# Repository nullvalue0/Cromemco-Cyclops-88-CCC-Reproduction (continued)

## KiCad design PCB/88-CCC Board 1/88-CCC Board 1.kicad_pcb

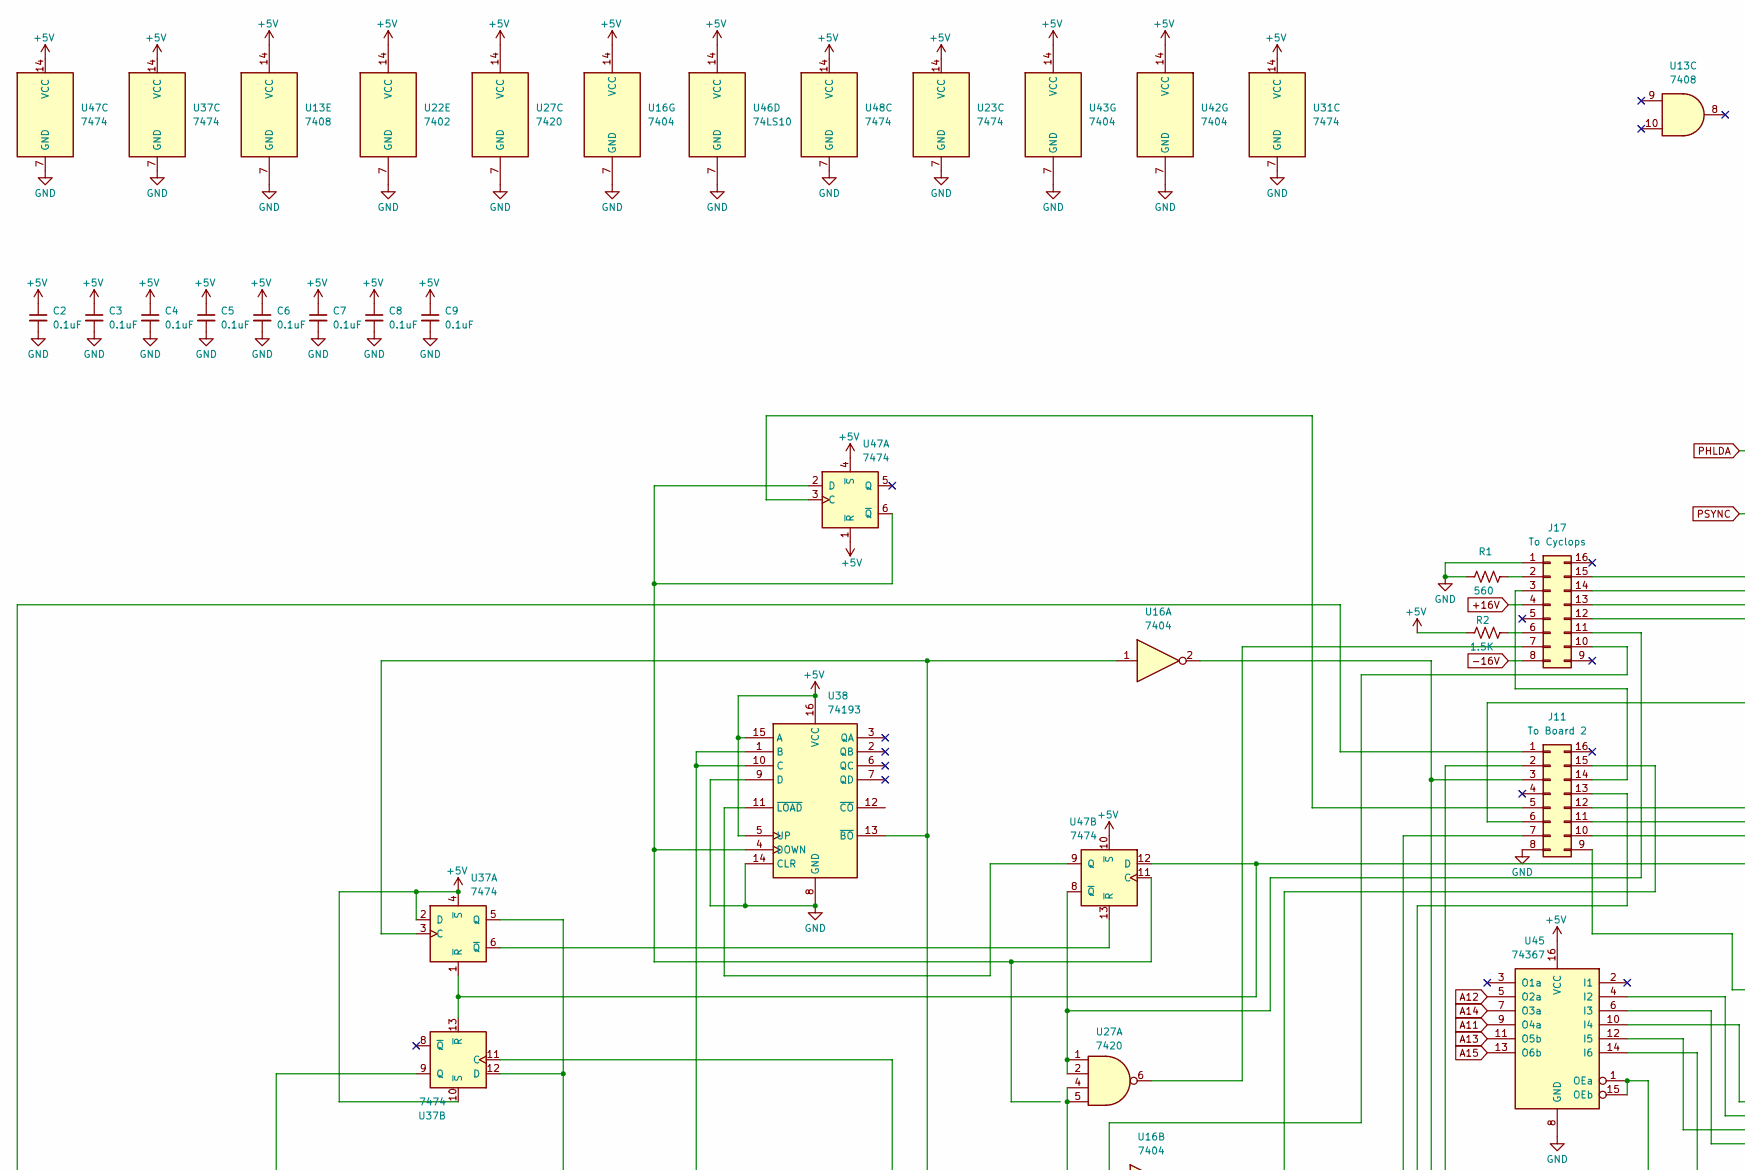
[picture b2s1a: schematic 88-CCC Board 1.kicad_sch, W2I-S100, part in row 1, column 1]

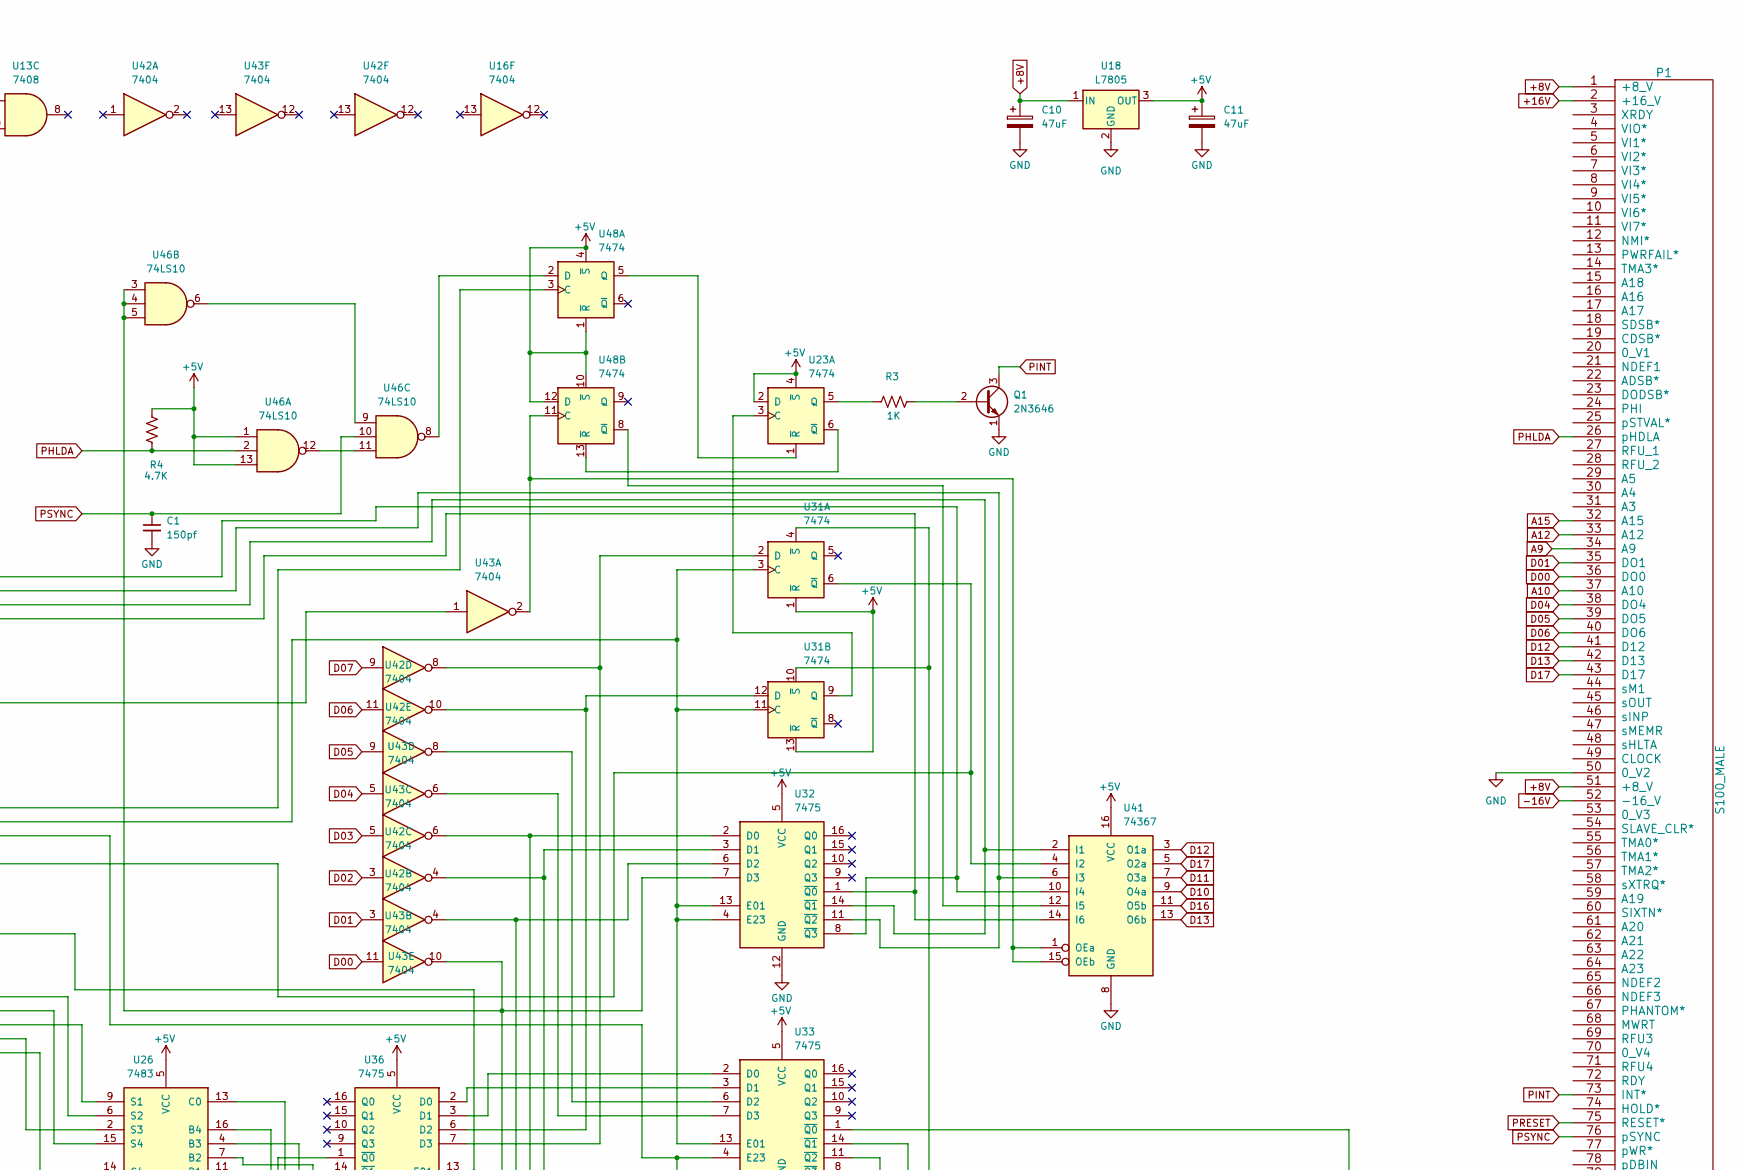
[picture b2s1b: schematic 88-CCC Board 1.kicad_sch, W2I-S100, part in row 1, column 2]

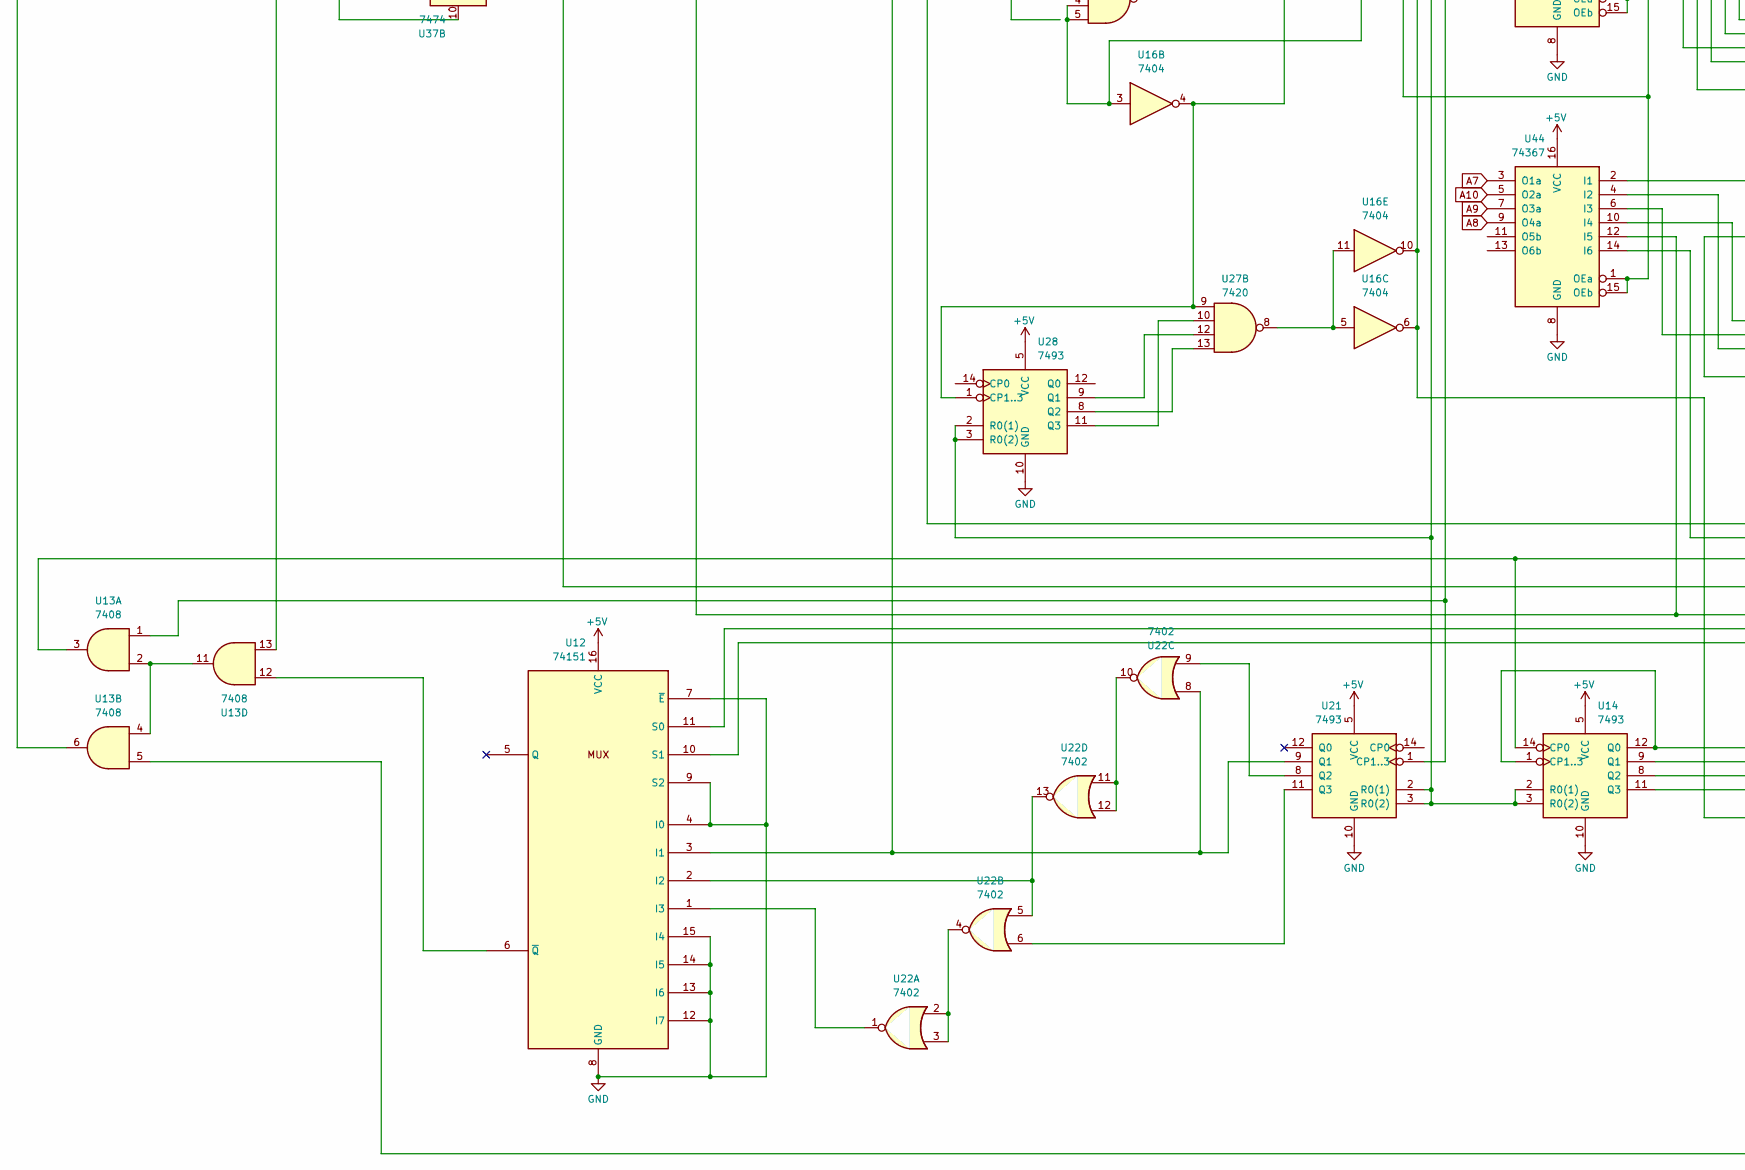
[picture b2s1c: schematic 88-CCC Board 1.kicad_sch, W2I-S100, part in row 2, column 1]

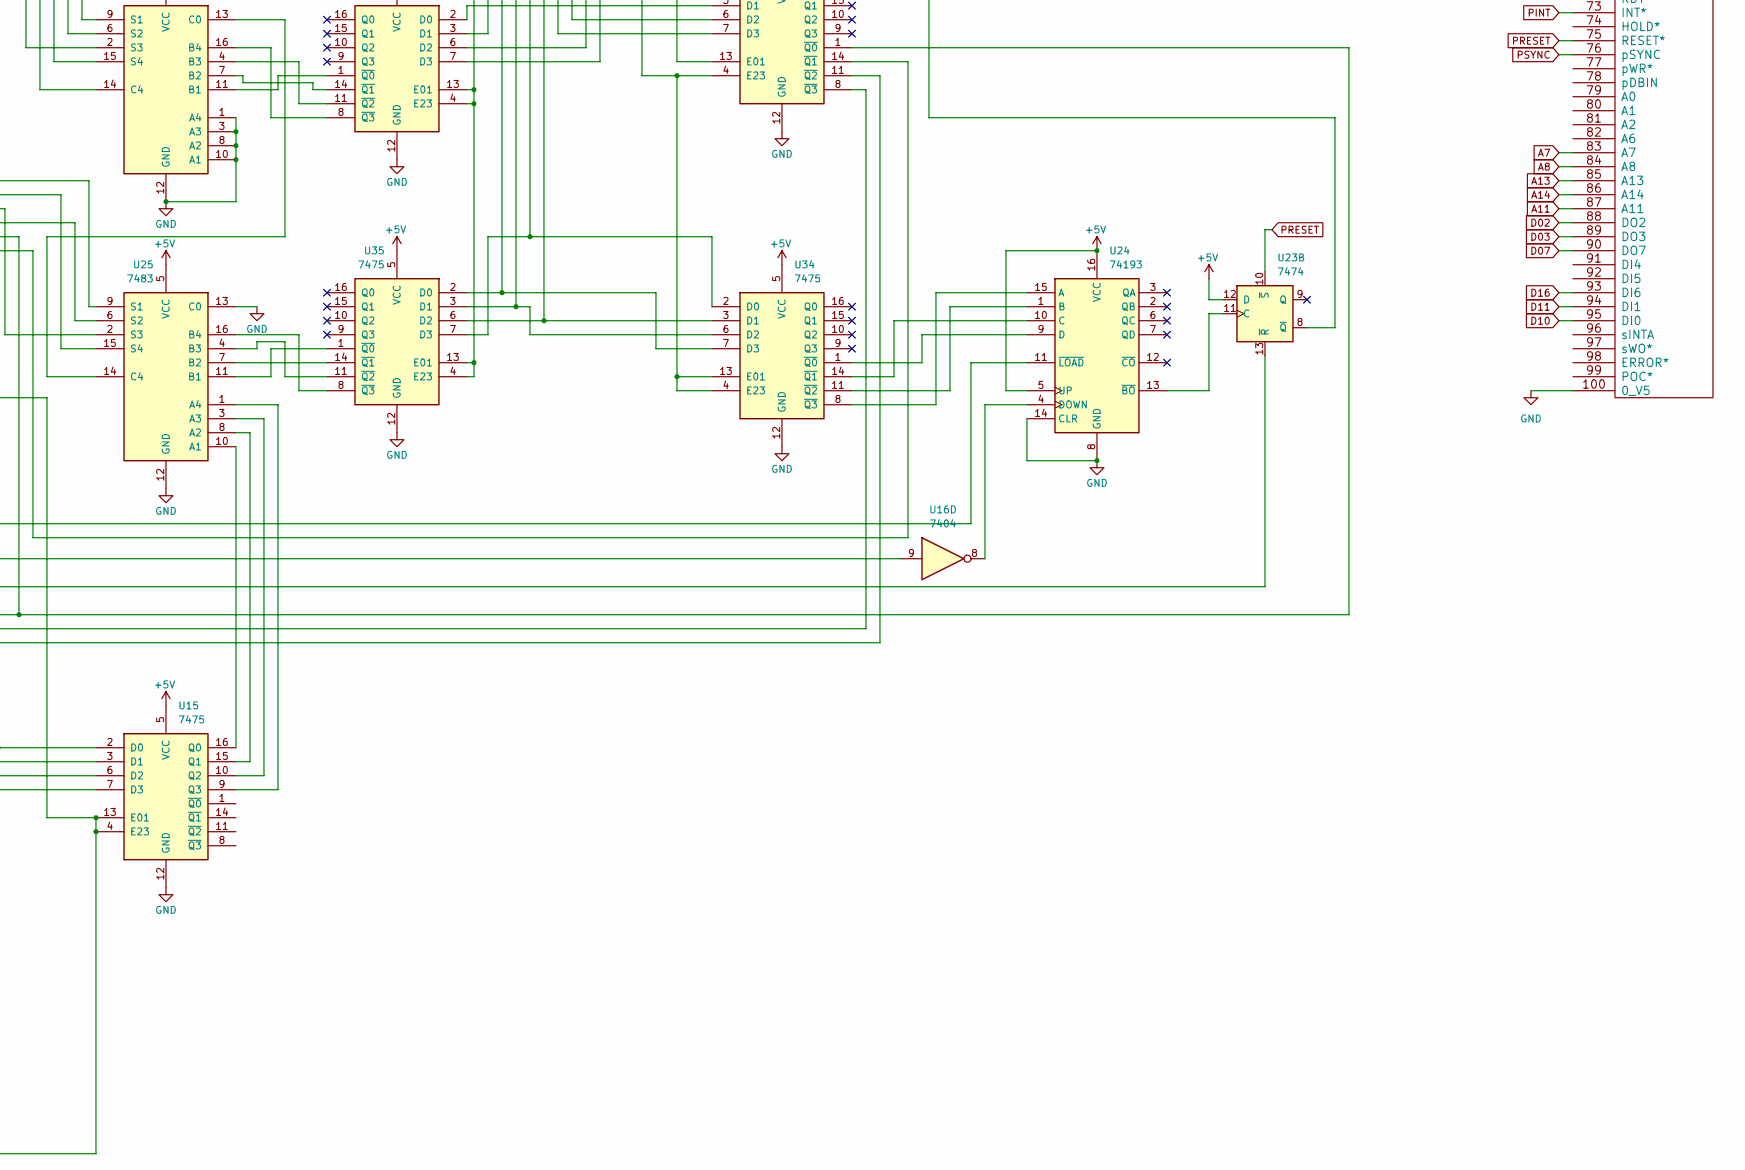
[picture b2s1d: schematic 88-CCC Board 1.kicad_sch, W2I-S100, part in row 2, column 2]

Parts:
C1: 150pf; C_Disc_D7.5mm_W5.0mm_P7.50mm
C2, C3, C4, C5, C6, C7, C8, C9: 0.1uF; C_Disc_D7.5mm_W5.0mm_P7.50mm
C10, C11: 47uF; C_Axial_L17.0mm_D7.0mm_P25.00mm_Horizontal
J11: To Board 2; DIP-16_W7.62mm
J17: To Cyclops; DIP-16_W7.62mm
P1: S100_MALE
Q1: 2N3646; TO-92
R1: 560; R_Axial_DIN0207_L6.3mm_D2.5mm_P10.16mm_Horizontal
R2: 1.5K; R_Axial_DIN0207_L6.3mm_D2.5mm_P10.16mm_Horizontal
R3: 1K; R_Axial_DIN0207_L6.3mm_D2.5mm_P10.16mm_Horizontal
R4: 4.7K; R_Axial_DIN0207_L6.3mm_D2.5mm_P10.16mm_Horizontal
U12: 74151; DIP-16_W7.62mm
U13: 7408; DIP-14_W7.62mm
U14, U21, U28: 7493; DIP-14_W7.62mm
U15, U32, U33, U34, U35, U36: 7475; DIP-16_W7.62mm
U16, U42, U43: 7404; DIP-14_W7.62mm
U18: L7805; TO-220-3_Horizontal_TabDown
U22: 7402; DIP-14_W7.62mm
U23, U31, U37, U47, U48: 7474; DIP-14_W7.62mm
U24, U38: 74193; DIP-16_W7.62mm
U25, U26: 7483; DIP-16_W7.62mm
U27: 7420; DIP-14_W7.62mm
U41, U44, U45: 74367; DIP-16_W7.62mm
U46: 74LS10; DIP-14_W7.62mm

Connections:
+5V: C2.1, C3.1, C4.1, C5.1, C6.1, C7.1, C8.1, C9.1, C11.1, R2.1, R4.1, U12.16 (VCC), U13.14 (VCC), U14.5 (VCC), U15.5 (VCC), U16.14 (VCC), U18.3 (OUT), U21.5 (VCC), U22.14 (VCC), U23.2 (D), U23.4 (~S), U23.12 (D), U23.14 (VCC), U24.5 (UP), U24.16 (VCC), U25.5 (VCC), U26.5 (VCC), U27.14 (VCC), U28.5 (VCC), U31.1 (~R), U31.13 (~R), U31.14 (VCC), U32.5 (VCC), U33.5 (VCC), U34.5 (VCC), U35.5 (VCC), U36.5 (VCC), U37.2 (D), U37.4 (~S), U37.10 (~S), U37.14 (VCC), U38.5 (UP), U38.15 (A), U38.16 (VCC), U41.16 (VCC), U42.14 (VCC), U43.14 (VCC), U44.16 (VCC), U45.16 (VCC), U46.1, U46.13, U46.14 (VCC), U47.1 (~R), U47.4 (~S), U47.10 (~S), U47.14 (VCC), U48.1 (~R), U48.4 (~S), U48.10 (~S), U48.12 (D), U48.14 (VCC)
+8V: C10.1, P1.1 (+8_V), P1.51 (+8_V), U18.1 (IN)
+16V: J17.4, P1.2 (+16_V)
-16V: J17.8, P1.52 (-16_V)
A7: P1.83 (A7), U44.3 (O1a)
A8: P1.84 (A8), U44.9 (O4a)
A9: P1.34 (A9), U44.7 (O3a)
A10: P1.37 (A10), U44.5 (O2a)
A11: P1.87 (A11), U45.9 (O4a)
A12: P1.33 (A12), U45.5 (O2a)
A13: P1.85 (A13), U45.11 (O5b)
A14: P1.86 (A14), U45.7 (O3a)
A15: P1.32 (A15), U45.13 (O6b)
D00: P1.36 (DO0), U43.11
D01: P1.35 (DO1), U43.3
D02: P1.88 (DO2), U42.3
D03: P1.89 (DO3), U42.5
D04: P1.38 (DO4), U43.5
D05: P1.39 (DO5), U43.9
D06: P1.40 (DO6), U42.11
D07: P1.90 (DO7), U42.9
D10: P1.95 (DI0), U41.9 (O4a)
D11: P1.94 (DI1), U41.7 (O3a)
D12: P1.41 (D12), U41.3 (O1a)
D13: P1.42 (D13), U41.13 (O6b)
D16: P1.93 (DI6), U41.11 (O5b)
D17: P1.43 (D17), U41.5 (O2a)
GND: C1.2, C2.2, C3.2, C4.2, C5.2, C6.2, C7.2, C8.2, C9.2, C10.2, C11.2, J11.8, J17.1, P1.50 (0_V2), P1.100 (0_V5), Q1.1 (E), R1.1, U12.4 (I0), U12.7 (~E), U12.8 (GND), U12.9 (S2), U12.12 (I7), U12.13 (I6), U12.14 (I5), U12.15 (I4), U13.7 (GND), U14.10 (GND), U15.12 (GND), U16.7 (GND), U18.2 (GND), U21.10 (GND), U22.7 (GND), U23.7 (GND), U24.8 (GND), U24.14 (CLR), U25.12 (GND), U25.13 (C0), U26.1 (A4), U26.3 (A3), U26.8 (A2), U26.10 (A1), U26.12 (GND), U27.7 (GND), U28.10 (GND), U31.7 (GND), U32.12 (GND), U33.12 (GND), U34.12 (GND), U35.12 (GND), U36.12 (GND), U37.7 (GND), U38.8 (GND), U38.9 (D), U38.14 (CLR), U41.8 (GND), U42.7 (GND), U43.7 (GND), U44.8 (GND), U45.8 (GND), U46.7 (GND), U47.7 (GND), U48.7 (GND)
unnamed: J11.1, U13.6
unnamed: J11.2, U13.1, U21.1 (CP1..3)
unnamed: J11.3, U14.2 (R0(1)), U14.3 (R0(2)), U16.2, U21.2 (R0(1)), U21.3 (R0(2)), U28.2 (R0(1)), U28.3 (R0(2))
unnamed: J11.5, U47.3 (C)
unnamed: J11.6, U43.1
unnamed: J11.7, U44.1 (OEa), U44.15 (OEb), U45.1 (OEa), U45.15 (OEb)
unnamed: J11.9, U35.4 (E23), U35.13 (E01), U36.4 (E23), U36.13 (E01)
unnamed: J11.10, U33.4 (E23), U34.4 (E23), U34.13 (E01)
unnamed: J11.11, U31.3 (C), U31.11 (C), U32.4 (E23), U32.13 (E01), U33.13 (E01)
unnamed: J11.12, U48.3 (C)
unnamed: J11.13, U13.5, U15.4 (E23), U15.13 (E01), U16.6, U16.10
unnamed: J11.14, J17.3
unnamed: J11.15, U16.4, U27.9, U28.1 (CP1..3)
unnamed: J17.2, R1.2
unnamed: J17.6, R2.2
unnamed: J17.7, U27.6
unnamed: J17.10, U16.3, U27.4, U27.5
unnamed: J17.11, U27.1, U27.2, U47.8 (~Q)
unnamed: J17.12, U32.1 (~Q0), U41.14 (I6)
unnamed: J17.13, U32.14 (~Q1), U41.2 (I1)
unnamed: J17.14, U32.11 (~Q2), U41.6 (I3)
unnamed: J17.15, U32.8 (~Q3), U41.10 (I4)
unnamed: Q1.2 (B), R3.2
unnamed: U12.3 (I1), U21.9 (Q1), U22.8, U37.11 (C)
unnamed: U12.2 (I2), U22.5, U22.13
unnamed: U12.1 (I3), U22.1
unnamed: U12.11 (S0), U33.8 (~Q3)
unnamed: U12.10 (S1), U33.11 (~Q2)
unnamed: U12.6 (~Q), U13.12
unnamed: U13.2, U13.4, U13.11
unnamed: U13.3, U14.14 (CP0), U16.9
unnamed: U14.1 (CP1..3), U14.12 (Q0), U15.2 (D0)
unnamed: U14.9 (Q1), U15.3 (D1)
unnamed: U14.8 (Q2), U15.6 (D2)
unnamed: U14.11 (Q3), U15.7 (D3)
unnamed: U15.16 (Q0), U25.10 (A1)
unnamed: U15.15 (Q1), U25.8 (A2)
unnamed: U15.10 (Q2), U25.3 (A3)
unnamed: U15.9 (Q3), U25.1 (A4)
unnamed: U16.5, U16.11, U27.8
unnamed: U21.8 (Q2), U22.9
unnamed: U21.11 (Q3), U22.6
unnamed: U22.2, U22.3, U22.4
unnamed: U22.10, U22.11, U22.12
unnamed: U23.3 (C), U31.9 (Q)
unnamed: R3.1, U23.5 (Q)
unnamed: U23.6 (~Q), U48.13 (~R)
unnamed: U23.1 (~R), U48.5 (Q)
unnamed: U23.11 (C), U24.13 (~BO)
unnamed: U23.8 (~Q), U31.4 (~S), U31.10 (~S)
unnamed: U23.13 (~R), U37.5 (Q), U37.12 (D)
unnamed: U24.15 (A), U34.8 (~Q3)
unnamed: U24.1 (B), U34.11 (~Q2)
unnamed: U24.10 (C), U34.14 (~Q1)
unnamed: U24.9 (D), U34.1 (~Q0)
unnamed: U16.8, U24.4 (DOWN)
unnamed: U16.1, U24.11 (~LOAD), U37.3 (C), U38.13 (~BO)
unnamed: U25.11 (B1), U35.1 (~Q0)
unnamed: U25.7 (B2), U35.14 (~Q1)
unnamed: U25.4 (B3), U35.11 (~Q2)
unnamed: U25.16 (B4), U35.8 (~Q3)
unnamed: U25.14 (C4), U26.13 (C0)
unnamed: U25.9 (S1), U44.2 (I1)
unnamed: U25.6 (S2), U44.10 (I4)
unnamed: U25.2 (S3), U44.6 (I3)
unnamed: U25.15 (S4), U44.4 (I2)
unnamed: U26.11 (B1), U36.1 (~Q0)
unnamed: U26.7 (B2), U36.14 (~Q1)
unnamed: U26.4 (B3), U36.11 (~Q2)
unnamed: U26.16 (B4), U36.8 (~Q3)
unnamed: U26.14 (C4), U45.14 (I6)
unnamed: U26.9 (S1), U45.10 (I4)
unnamed: U26.6 (S2), U45.4 (I2)
unnamed: U26.2 (S3), U45.12 (I5)
unnamed: U26.15 (S4), U45.6 (I3)
unnamed: U27.12, U28.9 (Q1)
unnamed: U27.13, U28.8 (Q2)
unnamed: U27.10, U28.11 (Q3)
unnamed: U31.2 (D), U36.7 (D3), U42.8
unnamed: U31.6 (~Q), U37.1 (~R), U37.13 (~R), U41.4 (I2), U47.12 (D)
unnamed: U31.12 (D), U36.6 (D2), U42.10
unnamed: U32.2 (D0), U34.2 (D0), U35.7 (D3), U42.6
unnamed: U32.3 (D1), U34.3 (D1), U35.6 (D2), U42.4
unnamed: U32.6 (D2), U34.6 (D2), U35.3 (D1), U43.4
unnamed: U32.7 (D3), U34.7 (D3), U35.2 (D0), U43.10, U46.3, U46.4, U46.5
unnamed: U33.2 (D0), U36.3 (D1)
unnamed: U33.3 (D1), U36.2 (D0)
unnamed: U33.6 (D2), U43.8
unnamed: U33.7 (D3), U43.6
unnamed: U33.1 (~Q0), U38.1 (B), U38.10 (C), U44.12 (I5)
unnamed: U33.14 (~Q1), U44.14 (I6)
unnamed: U37.6 (~Q), U47.13 (~R)
unnamed: U13.13, U37.9 (Q)
unnamed: U38.4 (DOWN), U47.2 (D), U47.6 (~Q), U47.11 (C)
unnamed: U38.11 (~LOAD), U47.9 (Q)
unnamed: U41.12 (I5), U48.8 (~Q)
unnamed: U41.1 (OEa), U41.15 (OEb), U43.2, U48.11 (C)
unnamed: U46.6, U46.9
unnamed: U46.11, U46.12
unnamed: U46.8, U48.2 (D)
PHLDA: P1.26 (pHDLA), R4.2, U46.2
PINT: P1.73 (INT*), Q1.3 (C)
PRESET: P1.75 (RESET*), U23.10 (~S)
PSYNC: C1.1, P1.76 (pSYNC), U46.10

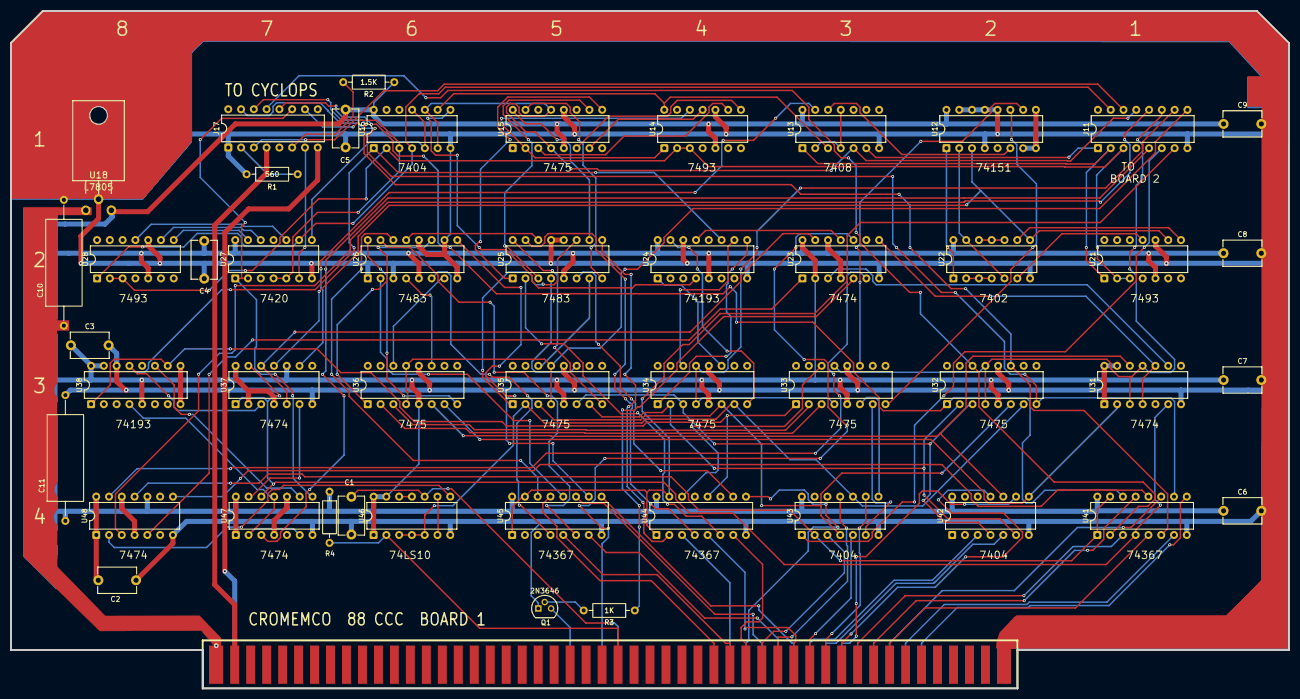
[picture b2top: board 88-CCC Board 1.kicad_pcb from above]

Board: 2 copper layers, 254.0 x 134.6 mm, 49 parts (0 on the bottom side), 132 nets.

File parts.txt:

CYCLOPS - Board 1

X 11 - To Board 2 DIP 16
X 12 - 74151
X 13 - 7408
X 14 - 7493
X 15 - 7475
X 16 - 7404
X 17 - To Cyclops DIP 16
X 18 - LM7805
  
X 21 - 7493
X 22 - 7402
X 23 - 7474
X 24 - 74193
X 25 - 7483
X 26 - 7483
X 27 - 7420
X 28 - 7493
  
X 31 - 7474
X 32 - 7475
X 33 - 7475
X 34 - 7475
X 35 - 7475
X 36 - 7475
X 37 - 7474
X 38 - 74193
  
X 41 - 74367
X 42 - 7404
X 43 - 7404
X 44 - 74367
X 45 - 74367
X 46 - 74LS10
X 47 - 7474
X 48 - 7474
  
  
CYCLOPS - Board 2
  
X 11 - To Board 1 DIP 16
X 12 - 7493
X 13 - 7493
X 14 - 7430
X 15 - 7430
X 16 - 7474
X 17 - 7474
X 18 - LM7805
  
X 21 - 74164
X 22 - 7475
X 23 - 7475
X 24 - 7402
X 25 - 7430
X 26 - 7474
X 27 - 7474
X 28 - 7400
  
X 31 - 7405
X 32 - 7475
X 33 - 7475
X 34 - 7410
X 35 - Port Select
X 36 - 7402
X 37 - 7400
X 38 - 7474
  
X 41 - 7405
X 42 - 74367
X 43 - 74367
X 44 - 74367
X 45 - 7404
X 46 - 7404
X 47 - 7405
X 48 - 7400

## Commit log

2025-12-06 Add README for Cromemco Cyclops 88-CCC project
2025-12-06 Fix Markdown links in README.md
2025-12-06 added more images
2025-12-06 Cleared PCB
2025-12-08 Board 1 schematic updates
2025-12-08 Board 1 Schematics Update
2025-12-08 Schematic updates
2025-12-10 Board 2 Schematics
2025-12-15 Board 2 schematic updates
2025-12-24 Board 1 PCB
2026-03-30 Reproduction PCBs Final
2026-04-21 Add image reference for 88 CCC reproduction boards
    Added image reference for 88 CCC reproduction boards.
2026-04-21 README
    Removed image reference for the 88 CCC reproduction boards.
